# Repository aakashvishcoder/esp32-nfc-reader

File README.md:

# ESP32 NFC Reader

This is my very own prototype of an NFC Reader, built using the ESP32 microcontroller! It’s a compact, wireless module designed to read and interact with NFC tags and cards. This board has several unique features and components (as listed below), and demonstrates how the ESP32 can be paired with an NFC front‑end chip to enable secure communication.

# Features:
- ESP32 microcontroller
- NFC transceiver chip
- PCB antenna
- Power management
- Interfaces
- Firmware support
- Form factor

# How to Use
Plug in a USB cable into the receptacle! Install the ESP32IDE for configuration of the firmware.

# Images

# BOM
## esp32-nfc-reader BOM

| Item | Description | Qty | Product link | Price w/ Tax ($) | Running Total |
|------|-------------|-----|--------------|------------------|---------------|
| Antenna | Antenna loop (Coilcraft MA5532-AE footprint) | 1 | [link](https://jlcpcb.com/) | $0.80 | $0.80 |
| Buzzer | 15×7.5 mm buzzer (THT) | 1 | [link](https://jlcpcb.com/partdetail/Jiangsu_HuanengElec-HND2319/C2878) | $1.20 | $2.00 |
| Capacitor | 0.1uF 0402 | 4 | [link](https://jlcpcb.com/partdetail/SamsungElectro-CL05B104KO5NNNC/C1525) | $0.40 | $2.40 |
| Capacitor | 47uF (closest available) | 1 | [link](https://jlcpcb.com/partdetail/DMBJ-RVT2A47M0607/C970653) | $0.50 | $2.90 |
| Capacitor | 1uF 0402 | 3 | [link](https://jlcpcb.com/partdetail/SamsungElectro-CL05A105KA5NQNC/C52923) | $0.12 | $3.02 |
| Capacitor | 4.7uF 0402 | 1 | [link](https://jlcpcb.com/partdetail/SamsungElectro-CL05A475MP5NRNC/C2835559) | $0.20 | $3.22 |
| Capacitor | 220pF 0402 | 1 | [link](https://jlcpcb.com/partdetail/YAGEO-CC0402KRX7R9BB221/C39122) | $0.08 | $3.30 |
| Capacitor | 100pF C0G 0402 | 1 | [link](https://jlcpcb.com/partdetail/YAGEO-CC0402JRNPO9BN101/C1546) | $0.08 | $3.38 |
| Capacitor | 10uF 0402 | 1 | [link](https://jlcpcb.com/partdetail/SamsungElectro-CL05A106MQ5NUNC/C15525) | $0.36 | $3.74 |
| Capacitor | 100nF 0402 | 1 | [link](https://jlcpcb.com/partdetail/SamsungElectro-CL05B104KO5NNNC/C1525) | $0.10 | $3.84 |
| Capacitor | 15pF NP0 0402 | 2 | [link](https://jlcpcb.com/partdetail/YAGEO-CC0402JRNPO9BN150/C1547) | $0.16 | $4.00 |
| Diode | Schottky 0402 | 1 | [link](https://jlcpcb.com/partdetail/onsemi-NSR05F40NXT5G/C146713) | $0.12 | $4.12 |
| Diode | Signal diode 0402 (closest) | 1 | [link](https://jlcpcb.com/partdetail/MicrodiodeElectronics-1N4148WS/C81598) | $0.10 | $4.22 |
| LED | WS2812B 5050 | 1 | [link](https://jlcpcb.com/partdetail/Worldsemi-WS2812B_BT/C2761795) | $0.30 | $4.52 |
| TVS diode | SMA 3.3V ESD/Surge | 1 | [link](https://jlcpcb.com/partdetail/TECHPUBLIC-TVS3V3L4U/C28642315) | $0.20 | $4.72 |
| Ferrite bead | 0402 | 1 | [link](https://jlcpcb.com/partdetail/Sunlord-SDCL1005C4N7STDF/C13595) | $0.20 | $4.92 |
| USB receptacle | USB‑C 16P (USB2.0) | 1 | [link](https://jlcpcb.com/partdetail/Korean_HropartsElec-TYPE_C_31_M12/C165948) | $1.50 | $6.42 |
| Header | 1×2 pin header 1.00 mm | 1 | [link](https://jlcpcb.com/partdetail/hanxia-HX_PZ1_27_1x2P_TPYQ/C41375972) | $0.05 | $6.47 |
| Header | 1×8 pin header 1.00 mm | 1 | [link](https://jlcpcb.com/partdetail/Kinghelm-KH_1_27PH180_1X8P_L72/C2938403) | $0.20 | $6.67 |
| Relay | Finder 34.51 SPDT (THT) | 1 | [link](https://jlcpcb.com/partdetail/Finder-34_51_7_0120010/C5512438) | $2.50 | $9.17 |
| Inductor | 4.7uH (closest SMD) | 1 | [link](https://jlcpcb.com/partdetail/CENKER-CKST0402_4_7uHM/C3002596) | $0.20 | $9.37 |
| Transistor | PMOS SOT‑23 (closest) | 1 | [link](https://jlcpcb.com/partdetail/JiangsuChangjingElec-SSM3J332R/C8548) | $0.15 | $9.52 |
| Transistor | NMOS SOT‑23 (2N7002) | 1 | [link](https://jlcpcb.com/partdetail/JiangsuChangjingElec-2N7002/C8545) | $0.15 | $9.67 |
| Resistor | 5.1k 0402 | 2 | [link](https://jlcpcb.com/partdetail/UNIROYAL-0402WGF5101TCE/C25905) | $0.04 | $9.71 |
| Resistor | 10k 0402 | 5 | [link](https://jlcpcb.com/partdetail/UNIROYAL-0402WGF1002TCE/C25804) | $0.55 | $10.26 |
| Resistor | 100k 0402 | 3 | [link](https://jlcpcb.com/partdetail/UNIROYAL-0402WGF1003TCE/C269673) | $0.36 | $10.62 |
| Resistor | 56k 0402 | 1 | [link](https://jlcpcb.com/partdetail/UNIROYAL-0402WGF5602TCE/C25796) | $0.12 | $10.74 |
| Resistor | 1.8k 0402 | 1 | [link](https://jlcpcb.com/partdetail/UNIROYAL-0105WHF1801TDE/C560335) | $0.10 | $10.84 |
| Resistor | 330 0402 | 1 | [link](https://jlcpcb.com/partdetail/UNIROYAL-0105WHF3300TDE/C560354) | $0.07 | $10.91 |
| Resistor | 220 0402 | 1 | [link](https://jlcpcb.com/partdetail/UNIROYAL-0105WHF2200TDE/C560342) | $0.07 | $10.98 |
| Switch | Tactile button (PTS636‑style) | 1 | [link](https://jlcpcb.com/partdetail/XKBConnectivity-TS_1187A_B_A_B/C318884) | $0.24 | $11.22 |
| Switch | Tactile button (PTS636‑style) | 1 | [link](https://jlcpcb.com/partdetail/XKBConnectivity-TS_1187A_B_A_B/C318884) | $0.24 | $11.46 |
| Switch | Tactile button (PTS636‑style) | 1 | [link](https://jlcpcb.com/partdetail/XKBConnectivity-TS_1187A_B_A_B/C318884) | $0.24 | $11.70 |
| Module | ESP32‑S3‑WROOM‑1 | 1 | [link](https://jlcpcb.com/partdetail/Espressif-ESP32_S3_WROOM_1/C2913198) | $4.50 | $16.20 |
| IC | Buck AP63203WU | 1 | [link](https://jlcpcb.com/partdetail/DiodesInc-AP63203WU7/C780769) | $0.60 | $16.

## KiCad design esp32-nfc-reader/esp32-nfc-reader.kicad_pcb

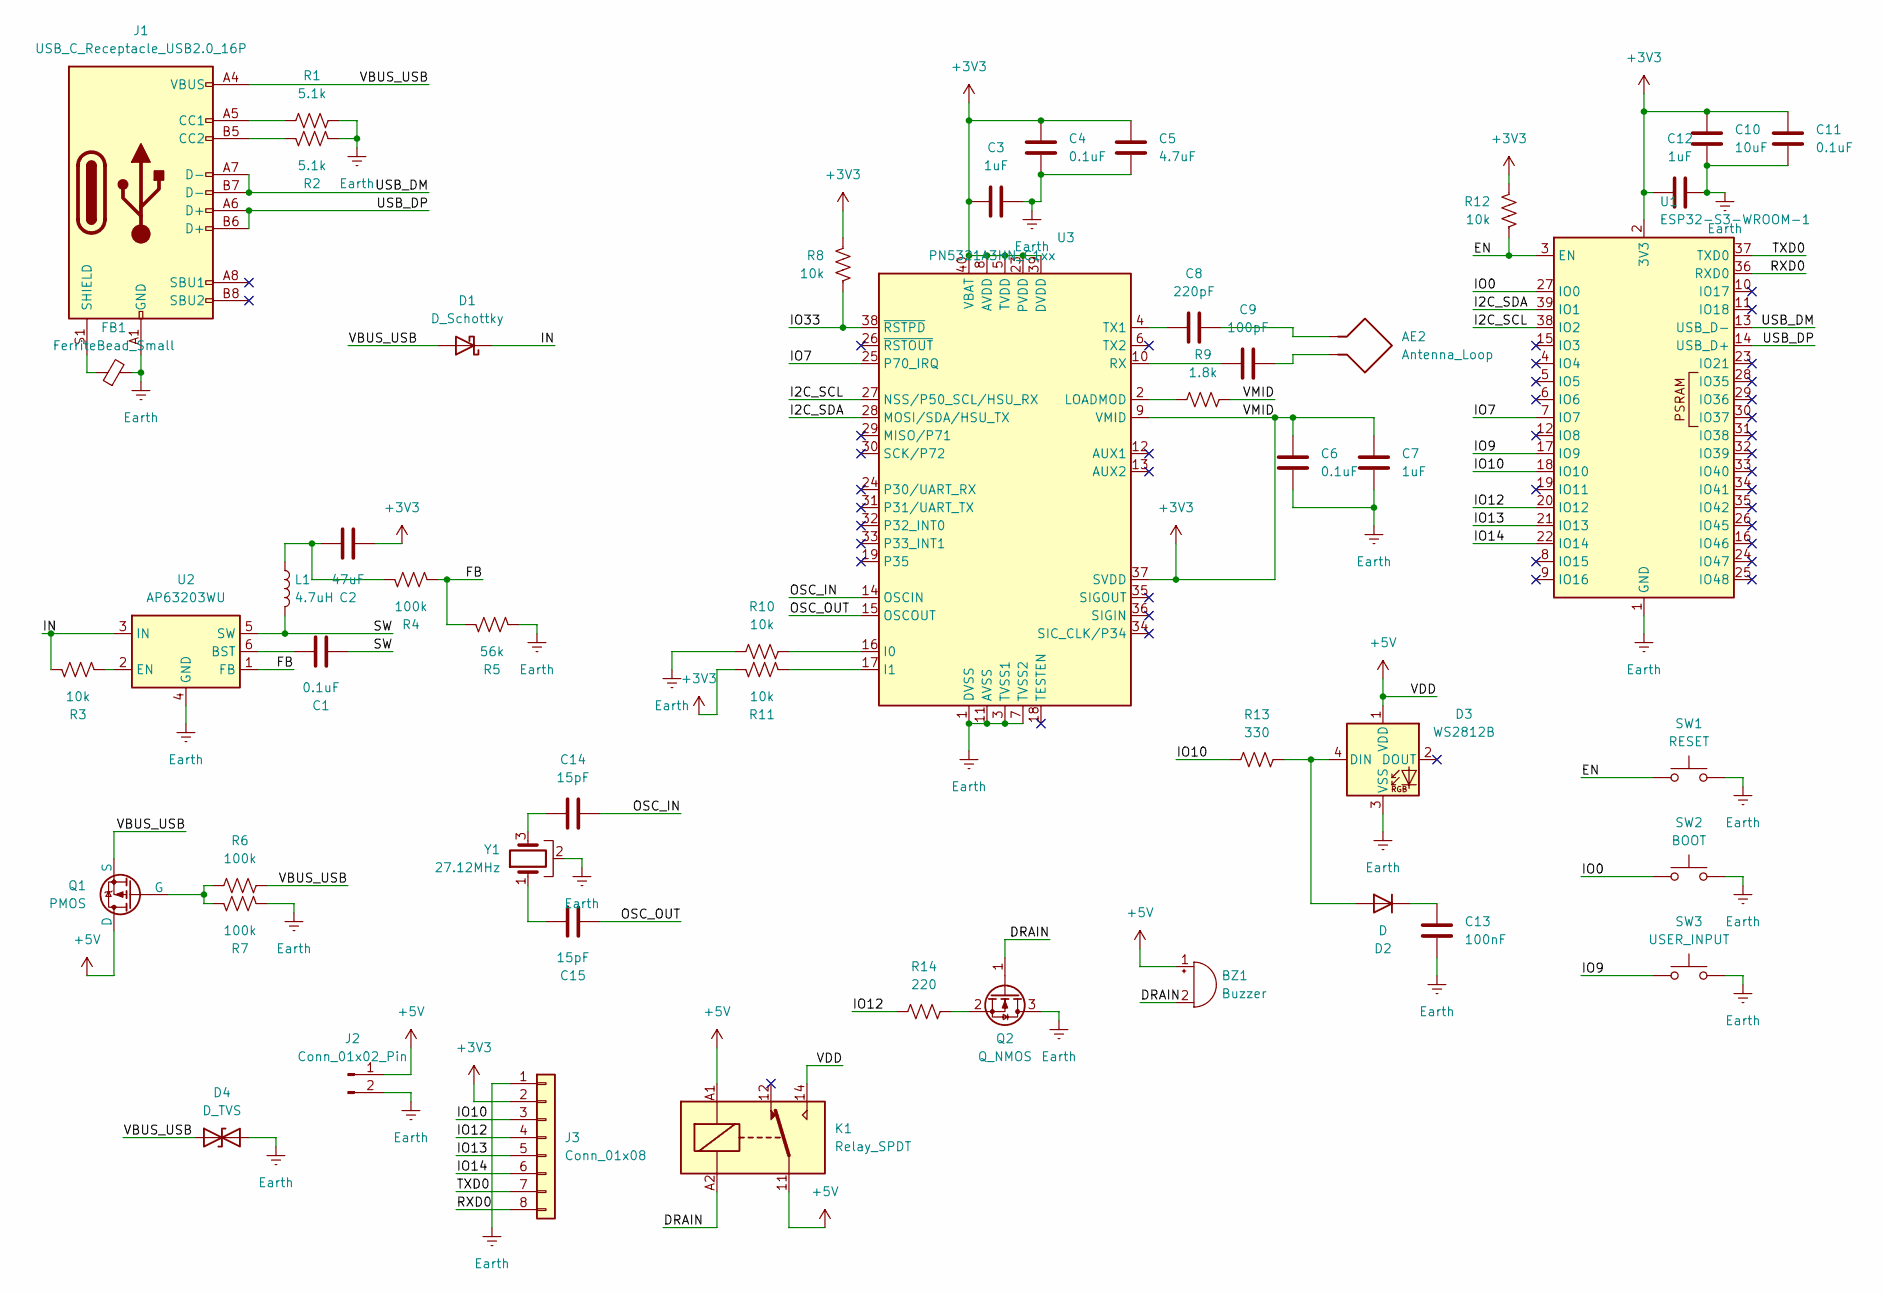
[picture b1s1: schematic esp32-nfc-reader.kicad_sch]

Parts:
AE2: Antenna_Loop; Coilcraft_MA5532-AE_RFID
BZ1: Buzzer; Buzzer_15x7.5RM7.6
C1, C4, C6, C11: 0.1uF; C_0402_1005Metric
C2: 47uF; C_0402_1005Metric
C3, C7, C12: 1uF; C_0402_1005Metric
C5: 4.7uF; C_0402_1005Metric
C8: 220pF; C_0402_1005Metric
C9: 100pF; C_0402_1005Metric
C10: 10uF; C_0402_1005Metric
C13: 100nF; C_0402_1005Metric
C14, C15: 15pF; C_0402_1005Metric
D1: D_Schottky; D_0402_1005Metric
D2: D; D_0402_1005Metric
D3: WS2812B; LED_WS2812B_PLCC4_5.0x5.0mm_P3.2mm
D4: D_TVS; D_SMA
FB1: FerriteBead_Small; L_0402_1005Metric
J1: USB_C_Receptacle_USB2.0_16P; USB_C_Receptacle_GCT_USB4105-xx-A_16P_TopMnt_Horizontal
J2: Conn_01x02_Pin; PinHeader_1x02_P1.00mm_Vertical
J3: Conn_01x08; PinHeader_1x08_P1.00mm_Vertical
K1: Relay_SPDT; Relay_SPDT_Finder_34.51_Vertical
L1: 4.7uH; L_0402_1005Metric
Q1: PMOS; SOT-23
Q2: Q_NMOS; SOT-23
R1, R2: 5.1k; R_0402_1005Metric
R3, R8, R10, R11, R12: 10k; R_0402_1005Metric
R4, R6, R7: 100k; R_0402_1005Metric
R5: 56k; R_0402_1005Metric
R9: 1.8k; R_0402_1005Metric
R13: 330; R_0402_1005Metric
R14: 220; R_0402_1005Metric
SW1: RESET; SW_Tactile_SPST_NO_Straight_CK_PTS636Sx25SMTRLFS
SW2: BOOT; SW_Tactile_SPST_NO_Straight_CK_PTS636Sx25SMTRLFS
SW3: USER_INPUT; SW_Tactile_SPST_NO_Straight_CK_PTS636Sx25SMTRLFS
U1: ESP32-S3-WROOM-1
U2: AP63203WU; TSOT-23-6
U3: PN5321A3HN_C1xx; HVQFN-40-1EP_6x6mm_P0.5mm_EP4.1x4.1mm
Y1: 27.12MHz; Crystal_HC49-U-3Pin_Vertical

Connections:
+3V3: C2.2, C3.1, C4.2, C5.2, C6.1, C7.1, C10.1, C11.1, C12.1, J3.2, R8.1, R9.2, R11.1, R12.1, U1.2 (3V3), U3.5 (TVDD), U3.8 (AVDD), U3.9 (VMID), U3.23 (PVDD), U3.37 (SVDD), U3.39 (DVDD), U3.40 (VBAT)
+5V: BZ1.1 (+), D3.1 (VDD), J2.1, K1.11, K1.14, K1.A1, Q1.1 (D)
/DRAIN: BZ1.2 (-), K1.A2, Q2.1 (G)
/EN: R12.2, SW1.1, U1.3 (EN)
/FB: R4.2, R5.1, U2.1 (FB)
/I2C_SCL: U1.38 (IO2), U3.27 (NSS/P50_SCL/HSU_RX)
/I2C_SDA: U1.39 (IO1), U3.28 (MOSI/SDA/HSU_TX)
/IN: D1.1 (K), R3.1, U2.3 (IN)
/IO0: SW2.1, U1.27 (IO0)
/IO7: U1.7 (IO7), U3.25 (P70_IRQ)
/IO9: SW3.1, U1.17 (IO9)
/IO10: J3.3, R13.1, U1.18 (IO10)
/IO12: J3.4, R14.1, U1.20 (IO12)
/IO13: J3.5, U1.21 (IO13)
/IO14: J3.6, U1.22 (IO14)
/IO33: R8.2, U3.38 (~RSTPD)
/OSC_IN: C14.2, U3.14 (OSCIN)
/OSC_OUT: C15.2, U3.15 (OSCOUT)
/RXD0: J3.8, U1.36 (RXD0)
/SW: C1.2, L1.2, U2.5 (SW)
/TXD0: J3.7, U1.37 (TXD0)
/USB_DM: J1.A7 (D-), J1.B7 (D-), U1.13 (USB_D-)
/USB_DP: J1.A6 (D+), J1.B6 (D+), U1.14 (USB_D+)
/VBUS_USB: D1.2 (A), D4.1 (A1), J1.A4 (VBUS), J1.A9 (VBUS), J1.B4 (VBUS), J1.B9 (VBUS), Q1.3 (S), R6.2
Earth: C3.2, C4.1, C5.1, C6.2, C7.2, C10.2, C11.2, C12.2, C13.2, D3.3 (VSS), D4.2 (A2), FB1.2, J1.A1 (GND), J1.A12 (GND), J1.B1 (GND), J1.B12 (GND), J2.2, J3.1, Q2.3 (D), R1.2, R2.2, R5.2, R7.1, R10.1, SW1.2, SW2.2, SW3.2, U1.1 (GND), U1.40 (GND), U1.41 (GND), U2.4 (GND), U3.1 (DVSS), U3.3 (TVSS1), U3.7 (TVSS2), U3.11 (AVSS), U3.41 (AVSS), Y1.2
unnamed: AE2.1, C8.2
unnamed: AE2.2, C9.1
unnamed: C2.1, L1.1, R4.1
unnamed: C14.1, Y1.3
unnamed: C15.1, Y1.1
unnamed: D2.2 (A), D3.4 (DIN), R13.2
unnamed: C13.1, D2.1 (K)
unnamed: J1.A5 (CC1), R1.1
unnamed: J1.B5 (CC2), R2.1
unnamed: FB1.1, J1.S1 (SHIELD)
unnamed: Q1.2 (G), R6.1, R7.2
unnamed: Q2.2 (S), R14.2
unnamed: C1.1, U2.6 (BST)
unnamed: R3.2, U2.2 (EN)
unnamed: R10.2, U3.16 (I0)
unnamed: R11.2, U3.17 (I1)
unnamed: R9.1, U3.2 (LOADMOD)
unnamed: C9.2, U3.10 (RX)
unnamed: C8.1, U3.4 (TX1)

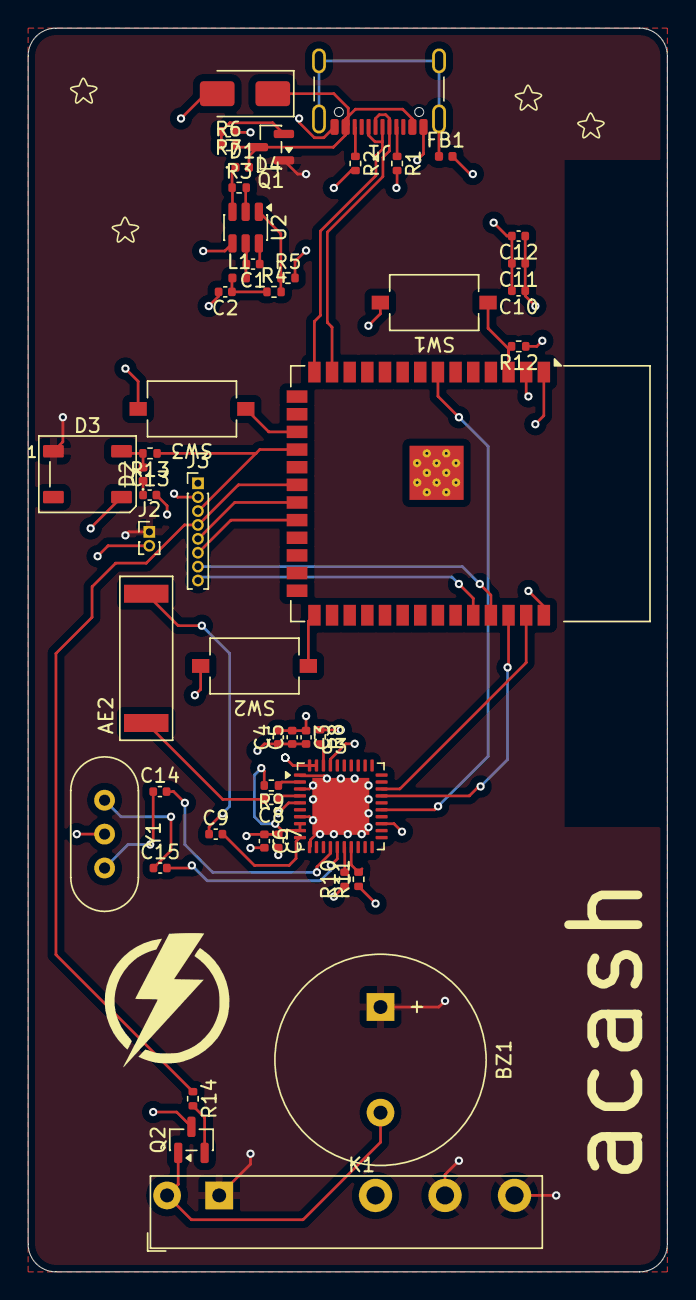
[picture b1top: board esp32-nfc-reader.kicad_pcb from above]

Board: 4 copper layers, 46.0 x 89.5 mm, 50 parts (0 on the bottom side), 44 nets.

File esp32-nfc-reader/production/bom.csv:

Designator,Footprint,Quantity,Value,LCSC Part #
AE2,Coilcraft_MA5532-AE_RFID,1,Antenna_Loop,
BZ1,Buzzer_15x7.5RM7.6,1,Buzzer,C2878
"C1,C11,C4,C6,C13",0402,5,100nF,C5142579
C10,0402,1,10uF,C466623
"C12,C3,C7",0402,3,1uF,C7503520
"C14,C15",0402,2,15pF,C3857558
C2,0402,1,47uF,C970653
C5,0402,1,4.7uF,C2835559
C8,0402,1,220pF,C39122
C9,0402,1,100pF,C1546
D1,0402,1,D_Schottky,C146713
D2,0402,1,D,
D3,LED_WS2812B_PLCC4_5.0x5.0mm_P3.2mm,1,WS2812B,C2761795
D4,D_SMA,1,D_TVS,C571370
FB1,0402,1,FerriteBead_Small,C32810416
J1,USB_C_Receptacle_GCT_USB4105-xx-A_16P_TopMnt_Horizontal,1,USB_C_Receptacle_USB2.0_16P,C3020560
J2,PinHeader_1x02_P1.00mm_Vertical,1,Conn_01x02_Pin,C41375972
J3,PinHeader_1x08_P1.00mm_Vertical,1,Conn_01x08,C2938403
K1,Relay_SPDT_Finder_34.51_Vertical,1,Relay_SPDT,C5512438
L1,0402,1,4.7uH,C3002596
Q1,SOT-23,1,PMOS,C5273673
Q2,SOT-23,1,Q_NMOS,C239054
"R1,R2",0402,2,5.1k,C25905
"R10,R11,R12,R3,R8",0402,5,10k,C2889342
R13,0402,1,330,C881128
R14,0402,1,220,C2938403
"R4,R6,R7",0402,3,100k,C269673
R5,0402,1,56k,C2889346
R9,0402,1,1.8k,C560335
SW1,SW_Tactile_SPST_NO_Straight_CK_PTS636Sx25SMTRLFS,1,RESET,C89380
SW2,SW_Tactile_SPST_NO_Straight_CK_PTS636Sx25SMTRLFS,1,BOOT,C89380
SW3,SW_Tactile_SPST_NO_Straight_CK_PTS636Sx25SMTRLFS,1,USER_INPUT,C89380
U1,ESP32-S3-WROOM-1,1,ESP32-S3-WROOM-1,C2913198
U2,TSOT-23-6,1,AP63203WU,C780769
U3,HVQFN-40-1EP_6x6mm_P0.5mm_EP4.1x4.1mm,1,PN5321A3HN_C1xx,C28925
Y1,Crystal_HC49-U-3Pin_Vertical,1,27.12MHz,C5265815

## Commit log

2025-11-29 completed pcb!
2025-11-29 Add README for ESP32 NFC Reader project
2025-11-30 Enhance README with features and usage details
    Added features list and usage instructions to README.
2025-11-30 Add BOM section to README
    Added a Bill of Materials (BOM) section with component details.
2025-12-01 added antenna loop
2025-12-01 Add new images and update BOM reference
2025-12-01 quick change to the pcb
2025-12-01 Update BOM table to include pricing information
    Added price and total cost columns to BOM table.
2025-12-01 Fix U1 component weight in README
2025-12-03 updated bom.csv
2025-12-03 readded the bom.csv (accidentally had it on the gitignore)
2025-12-03 added a gerber file
2025-12-03 added the finished bom + added gerbers + added production + fixed some other issues
2025-12-03 Revise README description for NFC Reader project
    Enhanced the project description to provide more detail about the NFC Reader's features and capabilities.
2025-12-04 fixed some issues with pcb
